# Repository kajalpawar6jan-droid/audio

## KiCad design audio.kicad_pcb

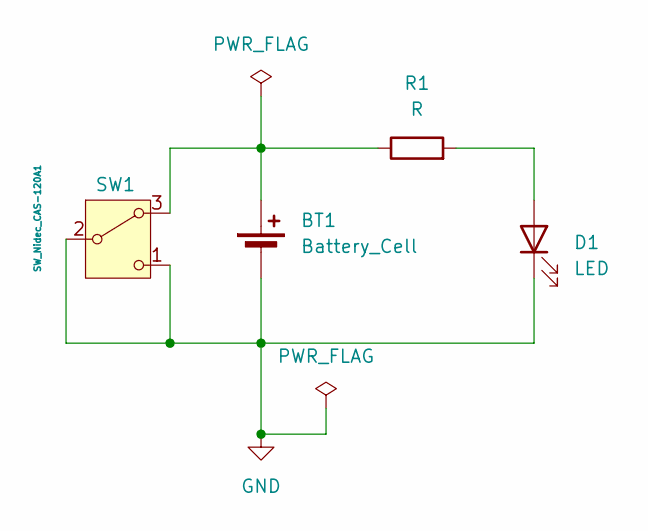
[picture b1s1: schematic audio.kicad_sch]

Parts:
BT1: Battery_Cell; BatteryHolder_Keystone_1042_1x18650
D1: LED; LED_D3.0mm
R1: R; R_LDR_4.9x4.2mm_P2.54mm_Vertical
SW1: SW_Nidec_CAS-120A1; Nidec_Copal_CAS-120A

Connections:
GND: BT1.2 (-), D1.1 (K), SW1.1 (C), SW1.2 (B)
unnamed: BT1.1 (+), R1.1, SW1.3 (A)
unnamed: D1.2 (A), R1.2

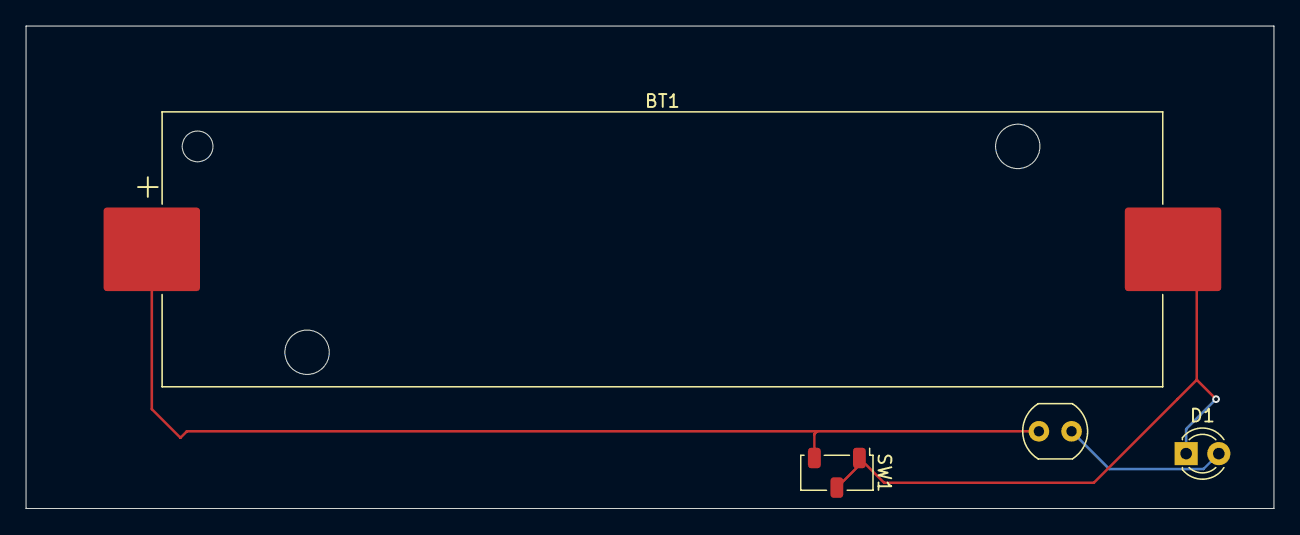
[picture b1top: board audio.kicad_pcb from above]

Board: 2 copper layers, 97.0 x 37.5 mm, 4 parts (0 on the bottom side), 3 nets.
